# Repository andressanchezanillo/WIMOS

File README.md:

# WIMOS
Wireless Monitoring System

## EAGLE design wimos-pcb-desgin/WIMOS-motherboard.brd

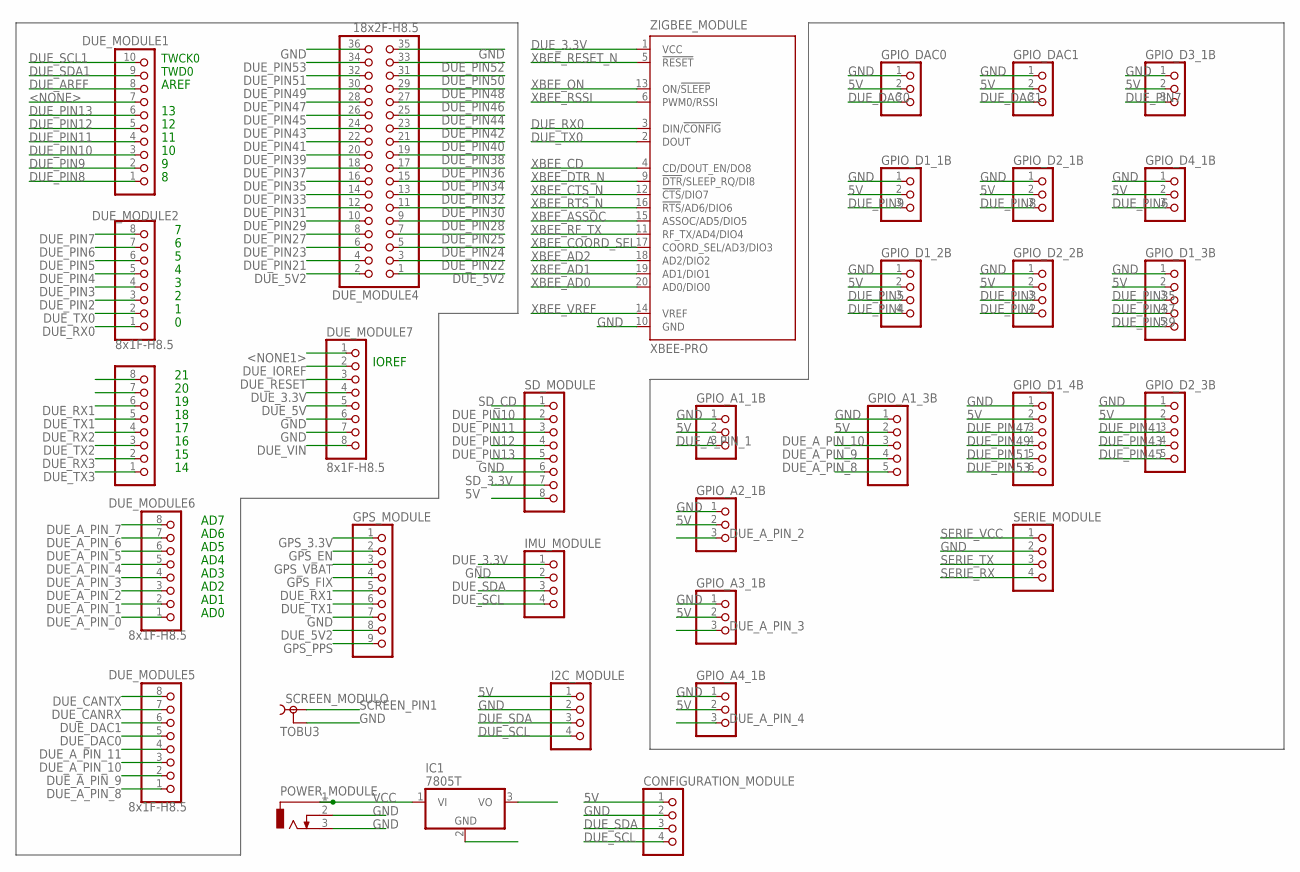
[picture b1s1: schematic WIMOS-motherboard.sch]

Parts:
CONFIGURATION_MODULE: PINHD-1X4; 1X04
DUE_MODULE1: 10x1F-H8.5; 1X10
DUE_MODULE2, DUE_MODULE3, DUE_MODULE5, DUE_MODULE6, DUE_MODULE7: 8x1F-H8.5; 1X08
DUE_MODULE4: 18x2F-H8.5; 2X18
GPIO_A1_1B, GPIO_A2_1B, GPIO_A3_1B, GPIO_A4_1B: PINHD-1X3/90; 1X03/90
GPIO_A1_3B: PINHD-1X5/90; 1X05/90
GPIO_D1_1B, GPIO_D2_1B, GPIO_D3_1B, GPIO_D4_1B: PINHD-1X3/90; 1X03/90
GPIO_D1_2B, GPIO_D2_2B: PINHD-1X4/90; 1X04/90
GPIO_D1_3B, GPIO_D2_3B: PINHD-1X5/90; 1X05/90
GPIO_D1_4B: PINHD-1X6/90; 1X06/90
GPIO_DAC0, GPIO_DAC1: PINHD-1X3/90; 1X03/90
GPS_MODULE: PINHD-1X9; 1X09
I2C_MODULE: PINHD-1X4/90; 1X04/90
IC1: 7805T; TO220H
IMU_MODULE: PINHD-1X4; 1X04
POWER_MODULE: DCJ0303
SCREEN_MODULO: TOBU3
SD_MODULE: PINHD-1X8; 1X08
SERIE_MODULE: PINHD-1X4/90; 1X04/90
ZIGBEE_MODULE: XBEE-PRO

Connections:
5V: CONFIGURATION_MODULE.1, GPIO_A1_1B.2, GPIO_A1_3B.2, GPIO_A2_1B.2, GPIO_A3_1B.2, GPIO_A4_1B.2, GPIO_D1_1B.2, GPIO_D1_2B.2, GPIO_D1_3B.2, GPIO_D1_4B.2, GPIO_D2_1B.2, GPIO_D2_2B.2, GPIO_D2_3B.2, GPIO_D3_1B.2, GPIO_D4_1B.2, GPIO_DAC0.2, GPIO_DAC1.2, I2C_MODULE.1, IC1.3 (VO), SD_MODULE.8
<NONE1>: DUE_MODULE7.1
<NONE>: DUE_MODULE1.7
DUE_3.3V: DUE_MODULE7.4, IMU_MODULE.1, ZIGBEE_MODULE.1 (VCC)
DUE_5V: DUE_MODULE7.5
DUE_5V2: DUE_MODULE4.1, DUE_MODULE4.2, GPS_MODULE.8
DUE_AREF: DUE_MODULE1.8
DUE_A_PIN_0: DUE_MODULE6.1
DUE_A_PIN_1: DUE_MODULE6.2, GPIO_A1_1B.3
DUE_A_PIN_2: DUE_MODULE6.3, GPIO_A2_1B.3
DUE_A_PIN_3: DUE_MODULE6.4, GPIO_A3_1B.3
DUE_A_PIN_4: DUE_MODULE6.5, GPIO_A4_1B.3
DUE_A_PIN_5: DUE_MODULE6.6
DUE_A_PIN_6: DUE_MODULE6.7
DUE_A_PIN_7: DUE_MODULE6.8
DUE_A_PIN_8: DUE_MODULE5.1, GPIO_A1_3B.5
DUE_A_PIN_9: DUE_MODULE5.2, GPIO_A1_3B.4
DUE_A_PIN_10: DUE_MODULE5.3, GPIO_A1_3B.3
DUE_A_PIN_11: DUE_MODULE5.4
DUE_CANRX: DUE_MODULE5.7
DUE_CANTX: DUE_MODULE5.8
DUE_DAC0: DUE_MODULE5.5, GPIO_DAC0.3
DUE_DAC1: DUE_MODULE5.6, GPIO_DAC1.3
DUE_IOREF: DUE_MODULE7.2
DUE_PIN2: DUE_MODULE2.3, GPIO_D2_2B.4
DUE_PIN3: DUE_MODULE2.4, GPIO_D2_2B.3
DUE_PIN4: DUE_MODULE2.5, GPIO_D1_2B.4
DUE_PIN5: DUE_MODULE2.6, GPIO_D1_2B.3
DUE_PIN6: DUE_MODULE2.7, GPIO_D4_1B.3
DUE_PIN7: DUE_MODULE2.8, GPIO_D3_1B.3
DUE_PIN8: DUE_MODULE1.1, GPIO_D2_1B.3
DUE_PIN9: DUE_MODULE1.2, GPIO_D1_1B.3
DUE_PIN10: DUE_MODULE1.3, SD_MODULE.2
DUE_PIN11: DUE_MODULE1.4, SD_MODULE.3
DUE_PIN12: DUE_MODULE1.5, SD_MODULE.4
DUE_PIN13: DUE_MODULE1.6, SD_MODULE.5
DUE_PIN21: DUE_MODULE4.4
DUE_PIN22: DUE_MODULE4.3
DUE_PIN23: DUE_MODULE4.6
DUE_PIN24: DUE_MODULE4.5
DUE_PIN25: DUE_MODULE4.7
DUE_PIN27: DUE_MODULE4.8
DUE_PIN28: DUE_MODULE4.9
DUE_PIN29: DUE_MODULE4.10
DUE_PIN30: DUE_MODULE4.11
DUE_PIN31: DUE_MODULE4.12
DUE_PIN32: DUE_MODULE4.13
DUE_PIN33: DUE_MODULE4.14
DUE_PIN34: DUE_MODULE4.15
DUE_PIN35: DUE_MODULE4.16, GPIO_D1_3B.3
DUE_PIN36: DUE_MODULE4.17
DUE_PIN37: DUE_MODULE4.18, GPIO_D1_3B.4
DUE_PIN38: DUE_MODULE4.19
DUE_PIN39: DUE_MODULE4.20, GPIO_D1_3B.5
DUE_PIN40: DUE_MODULE4.21
DUE_PIN41: DUE_MODULE4.22, GPIO_D2_3B.3
DUE_PIN42: DUE_MODULE4.23
DUE_PIN43: DUE_MODULE4.24, GPIO_D2_3B.4
DUE_PIN44: DUE_MODULE4.25
DUE_PIN45: DUE_MODULE4.26, GPIO_D2_3B.5
DUE_PIN46: DUE_MODULE4.27
DUE_PIN47: DUE_MODULE4.28, GPIO_D1_4B.3
DUE_PIN48: DUE_MODULE4.29
DUE_PIN49: DUE_MODULE4.30, GPIO_D1_4B.4
DUE_PIN50: DUE_MODULE4.31
DUE_PIN51: DUE_MODULE4.32, GPIO_D1_4B.5
DUE_PIN52: DUE_MODULE4.33
DUE_PIN53: DUE_MODULE4.34, GPIO_D1_4B.6
DUE_RESET: DUE_MODULE7.3
DUE_RX0: DUE_MODULE2.1, ZIGBEE_MODULE.3 (DIN/!CONFIG)
DUE_RX1: DUE_MODULE3.6, GPS_MODULE.5
DUE_RX2: DUE_MODULE3.4
DUE_RX3: DUE_MODULE3.2
DUE_SCL: CONFIGURATION_MODULE.4, DUE_MODULE3.8, I2C_MODULE.4, IMU_MODULE.4
DUE_SCL1: DUE_MODULE1.10
DUE_SDA: CONFIGURATION_MODULE.3, DUE_MODULE3.7, I2C_MODULE.3, IMU_MODULE.3
DUE_SDA1: DUE_MODULE1.9
DUE_TX0: DUE_MODULE2.2, ZIGBEE_MODULE.2 (DOUT)
DUE_TX1: DUE_MODULE3.5, GPS_MODULE.6
DUE_TX2: DUE_MODULE3.3
DUE_TX3: DUE_MODULE3.1
DUE_VIN: DUE_MODULE7.8
GND: CONFIGURATION_MODULE.2, DUE_MODULE4.35, DUE_MODULE4.36, DUE_MODULE7.6, DUE_MODULE7.7, GPIO_A1_1B.1, GPIO_A1_3B.1, GPIO_A2_1B.1, GPIO_A3_1B.1, GPIO_A4_1B.1, GPIO_D1_1B.1, GPIO_D1_2B.1, GPIO_D1_3B.1, GPIO_D1_4B.1, GPIO_D2_1B.1, GPIO_D2_2B.1, GPIO_D2_3B.1, GPIO_D3_1B.1, GPIO_D4_1B.1, GPIO_DAC0.1, GPIO_DAC1.1, GPS_MODULE.7, I2C_MODULE.2, IC1.2 (GND), IMU_MODULE.2, POWER_MODULE.2, POWER_MODULE.3, SCREEN_MODULO.2, SCREEN_MODULO.2@1 (2), SCREEN_MODULO.2@2 (2), SD_MODULE.6, SERIE_MODULE.2, ZIGBEE_MODULE.10 (GND)
GPS_3.3V: GPS_MODULE.1
GPS_EN: GPS_MODULE.2
GPS_FIX: GPS_MODULE.4
GPS_PPS: GPS_MODULE.9
GPS_VBAT: GPS_MODULE.3
SCREEN_PIN1: SCREEN_MODULO.1
SD_3.3V: SD_MODULE.7
SD_CD: SD_MODULE.1
SERIE_RX: SERIE_MODULE.4
SERIE_TX: SERIE_MODULE.3
SERIE_VCC: SERIE_MODULE.1
VCC: IC1.1 (VI), POWER_MODULE.1
XBEE_AD0: ZIGBEE_MODULE.20 (AD0/DIO0)
XBEE_AD1: ZIGBEE_MODULE.19 (AD1/DIO1)
XBEE_AD2: ZIGBEE_MODULE.18 (AD2/DIO2)
XBEE_ASSOC: ZIGBEE_MODULE.15 (ASSOC/AD5/DIO5)
XBEE_CD: ZIGBEE_MODULE.4 (CD/DOUT_EN/DO8)
XBEE_COORD_SEL: ZIGBEE_MODULE.17 (COORD_SEL/AD3/DIO3)
XBEE_CTS_N: ZIGBEE_MODULE.12 (!CTS!/DIO7)
XBEE_DTR_N: ZIGBEE_MODULE.9 (!DTR!/SLEEP_RQ/DI8)
XBEE_ON: ZIGBEE_MODULE.13 (ON/!SLEEP)
XBEE_RESET_N: ZIGBEE_MODULE.5 (!RESET)
XBEE_RF_TX: ZIGBEE_MODULE.11 (RF_TX/AD4/DIO4)
XBEE_RSSI: ZIGBEE_MODULE.6 (PWM0/RSSI)
XBEE_RTS_N: ZIGBEE_MODULE.16 (!RTS!/AD6/DIO6)
XBEE_VREF: ZIGBEE_MODULE.14 (VREF)

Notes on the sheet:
IOREF
TWCK0
TWD0
AD1
AD2
AD3
AD4
AD5
AD6
AD0
AREF
AD7

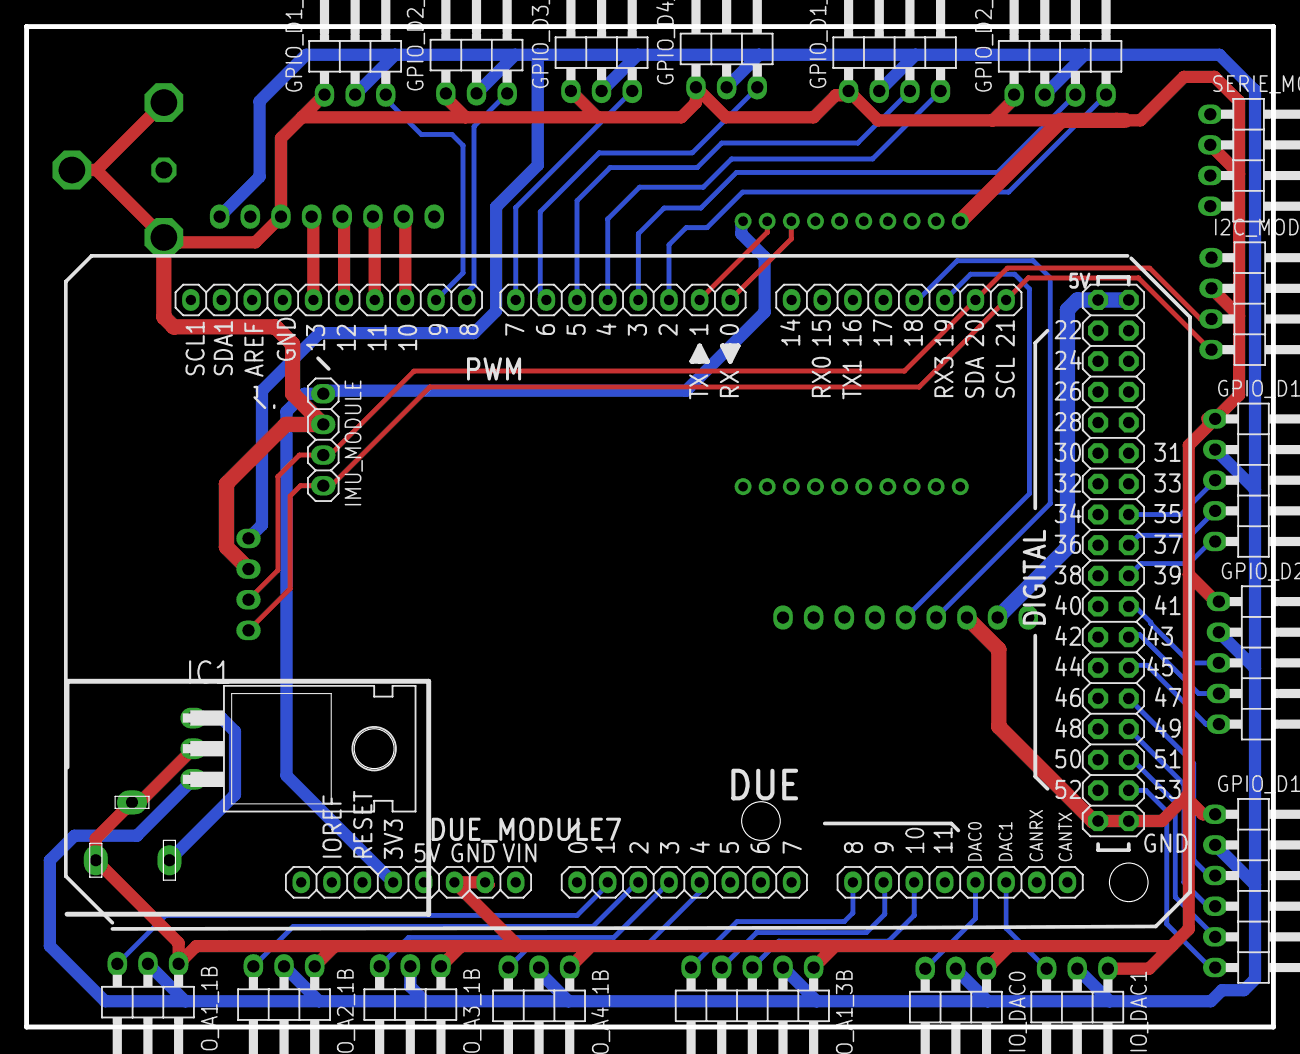
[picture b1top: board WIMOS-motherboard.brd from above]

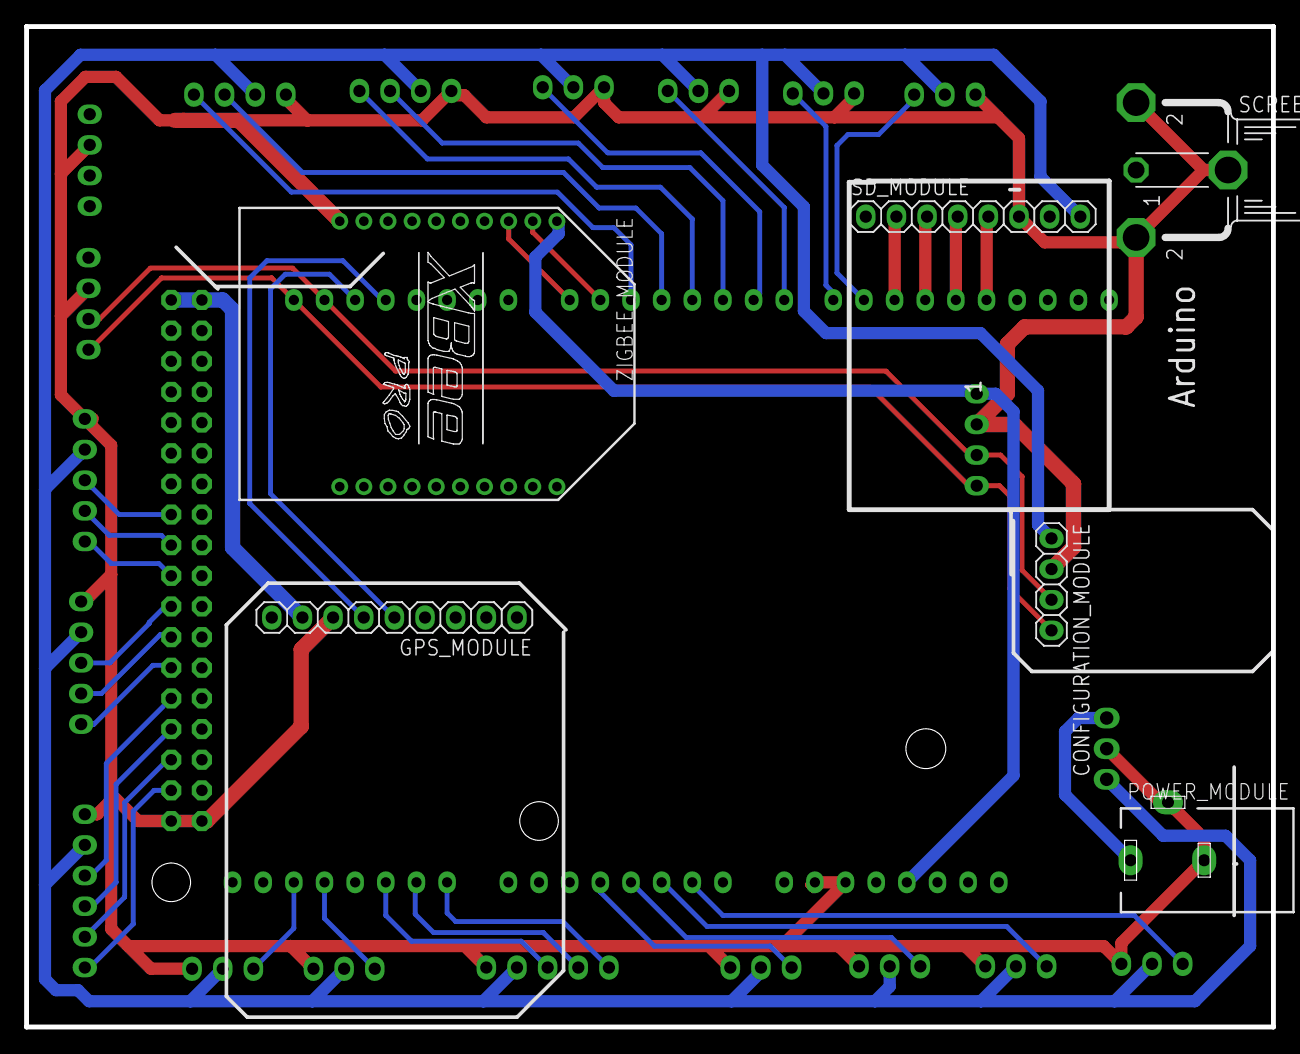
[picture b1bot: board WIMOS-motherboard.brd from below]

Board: 2 copper layers, 103.3 x 82.9 mm, 33 parts (6 on the bottom side), 42 nets.

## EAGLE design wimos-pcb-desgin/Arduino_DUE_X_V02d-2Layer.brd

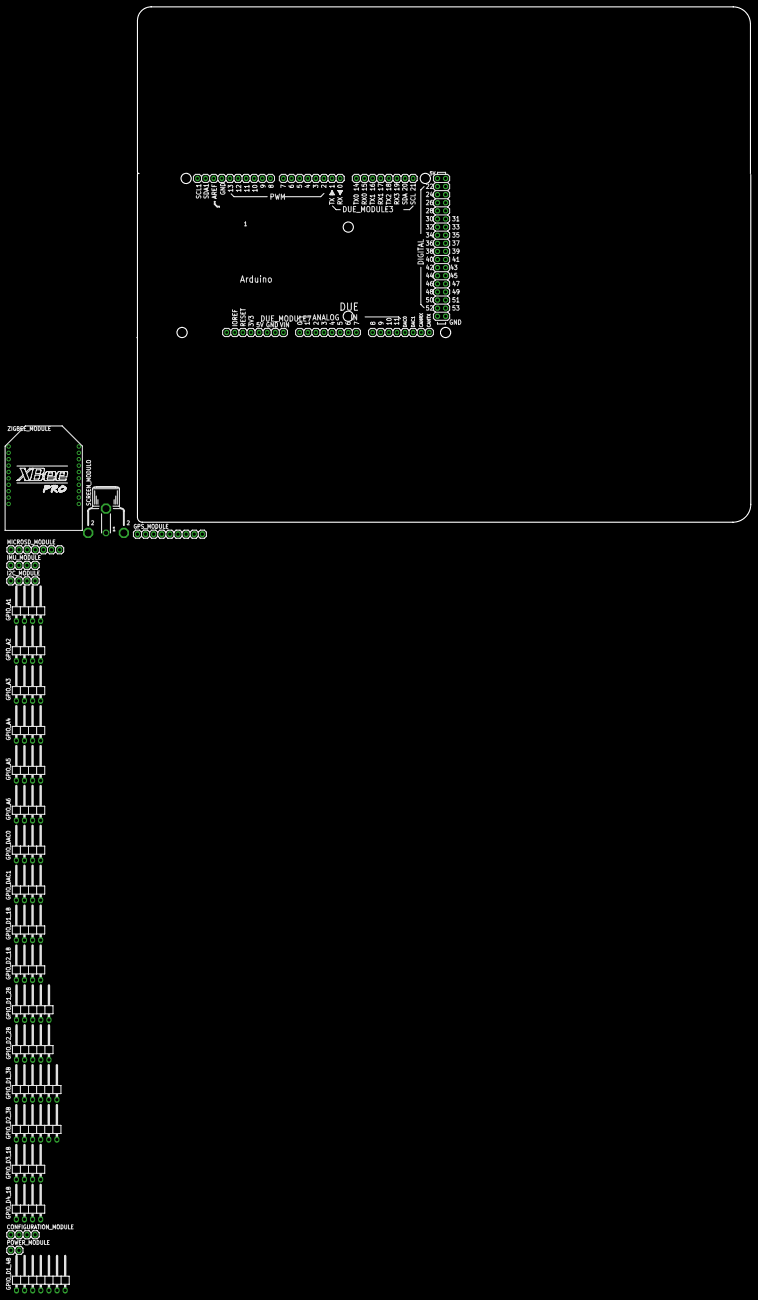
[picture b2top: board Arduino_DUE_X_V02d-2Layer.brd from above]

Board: 2 copper layers, 192.3 x 161.4 mm, 32 parts (0 on the bottom side), 8 nets, no tracks yet.

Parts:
CONFIGURATION_MODULE: 1X04
DUE_MODULE1: 10x1F-H8.5; 1X10
DUE_MODULE2, DUE_MODULE3, DUE_MODULE5, DUE_MODULE6, DUE_MODULE7: 8x1F-H8.5; 1X08
DUE_MODULE4: 18x2F-H8.5; 2X18
GPIO_A1, GPIO_A2, GPIO_A3, GPIO_A4, GPIO_A5, GPIO_A6: 1X04/90
GPIO_D1_1B, GPIO_D2_1B, GPIO_D3_1B, GPIO_D4_1B: 1X04/90
GPIO_D1_2B, GPIO_D2_2B: 1X05/90
GPIO_D1_3B, GPIO_D2_3B: 1X06/90
GPIO_D1_4B: 1X07/90
GPIO_DAC0, GPIO_DAC1: 1X04/90
GPS_MODULE: 1X09
I2C_MODULE: 1X04
IMU_MODULE: 1X04
MICROSD_MODULE: 1X07
POWER_MODULE: 1X02
SCREEN_MODULO: TOBU3
ZIGBEE_MODULE: XBEE-PRO

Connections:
DUE_5V: DUE_MODULE4.35, DUE_MODULE4.36, DUE_MODULE7.5
GND: CONFIGURATION_MODULE.2, DUE_MODULE4.1, DUE_MODULE4.2, DUE_MODULE7.6, DUE_MODULE7.7, GPIO_A1.4, GPIO_A2.4, GPIO_A3.4, GPIO_A4.4, GPIO_A5.4, GPIO_A6.4, GPIO_D1_1B.4, GPIO_D1_2B.5, GPIO_D1_3B.6, GPIO_D1_4B.7, GPIO_D2_1B.4, GPIO_D2_2B.5, GPIO_D2_3B.6, GPIO_D3_1B.4, GPIO_D4_1B.4, GPIO_DAC0.4, GPIO_DAC1.4, GPS_MODULE.7, I2C_MODULE.2, IMU_MODULE.2, MICROSD_MODULE.5, POWER_MODULE.2, ZIGBEE_MODULE.10
GPIO_3.3V: GPIO_A1.1, GPIO_A2.1, GPIO_A3.1, GPIO_A4.1, GPIO_A5.1, GPIO_A6.1, GPIO_D1_1B.1, GPIO_D1_2B.1, GPIO_D1_3B.1, GPIO_D1_4B.1, GPIO_D2_1B.1, GPIO_D2_2B.1, GPIO_D2_3B.1, GPIO_D3_1B.1, GPIO_D4_1B.1, GPIO_DAC0.1, GPIO_DAC1.1
GPIO_5V: GPIO_A1.2, GPIO_A2.2, GPIO_A3.2, GPIO_A4.2, GPIO_A5.2, GPIO_A6.2, GPIO_D1_1B.2, GPIO_D1_2B.2, GPIO_D1_3B.2, GPIO_D1_4B.2, GPIO_D2_1B.2, GPIO_D2_2B.2, GPIO_D2_3B.2, GPIO_D3_1B.2, GPIO_D4_1B.2, GPIO_DAC0.2, GPIO_DAC1.2
I2C_SCL: CONFIGURATION_MODULE.4, I2C_MODULE.4
I2C_SDA: CONFIGURATION_MODULE.3, I2C_MODULE.3
I2C_VCC: CONFIGURATION_MODULE.1, I2C_MODULE.1
SCREEN_PIN2: SCREEN_MODULO.2, SCREEN_MODULO.2@1, SCREEN_MODULO.2@2

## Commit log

2015-02-19 Diseño de la placa pcb del sistema
2015-02-25 Placa de circuito impreso
2015-03-04 Importar diagrama de gant y libreria arduino
